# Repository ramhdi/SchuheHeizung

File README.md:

# SchuheHeizung
DIY Thermostat - Applicable for shoe dryer, sous vide cooker, etc

## Arduino codes
- SchuheHeizung v1: first version, heating controlled by user via Blynk app, microcontroller using NodeMCU
- SchuheHeizung v2: offline heating control, uses OLED display and rotary encoder as user interface, microcontroller using Arduino Nano

## PCB files
- SH v1: first version, microcontroller using NodeMCU, controls DC fan and heater
- SH v2: microcontroller using Arduino Nano, controls AC fan and heater
- SH v3: microcontroller using NodeMCU, controls AC fan and heater

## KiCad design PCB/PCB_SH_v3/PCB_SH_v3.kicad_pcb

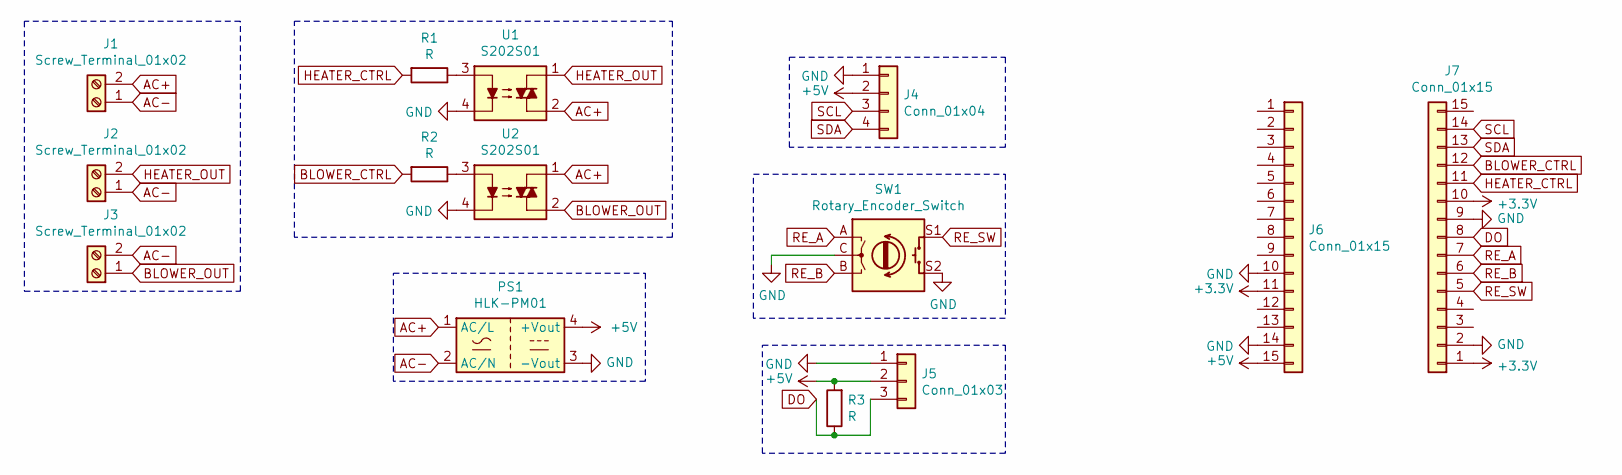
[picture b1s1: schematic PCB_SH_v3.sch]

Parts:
J1, J2, J3: Screw_Terminal_01x02; TerminalBlock_Wuerth_691311400102_P7.62mm
J4: Conn_01x04; PinSocket_1x04_P2.54mm_Vertical
J5: Conn_01x03; PinSocket_1x03_P2.54mm_Vertical
J6, J7: Conn_01x15; PinSocket_1x15_P2.54mm_Vertical
PS1: HLK-PM01; Converter_ACDC_HiLink_HLK-PMxx
R1, R2, R3: R; R_1206_3216Metric_Pad1.42x1.75mm_HandSolder
SW1: Rotary_Encoder_Switch; RotaryEncoder_Alps_EC11E-Switch_Vertical_H20mm
U1, U2: S202S01; SIP4_Sharp-SSR_P7.62mm_Straight

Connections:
+3V3: J6.11, J7.1, J7.10
+5V: J4.2, J5.2, J6.15, PS1.4 (+Vout), R3.2
AC+: J1.2, PS1.1 (AC/L), U1.2, U2.1
AC-: J1.1, J2.1, J3.2, PS1.2 (AC/N)
BLOWER_CTRL: J7.12, R2.2
BLOWER_OUT: J3.1, U2.2
DO: J5.3, J7.8, R3.1
GND: J4.1, J5.1, J6.10, J6.14, J7.2, J7.9, PS1.3 (-Vout), SW1.C, SW1.S2, U1.4, U2.4
HEATER_CTRL: J7.11, R1.2
HEATER_OUT: J2.2, U1.1
unnamed: R1.1, U1.3
unnamed: R2.1, U2.3
RE_A: J7.7, SW1.A
RE_B: J7.6, SW1.B
RE_SW: J7.5, SW1.S1
SCL: J4.3, J7.14
SDA: J4.4, J7.13

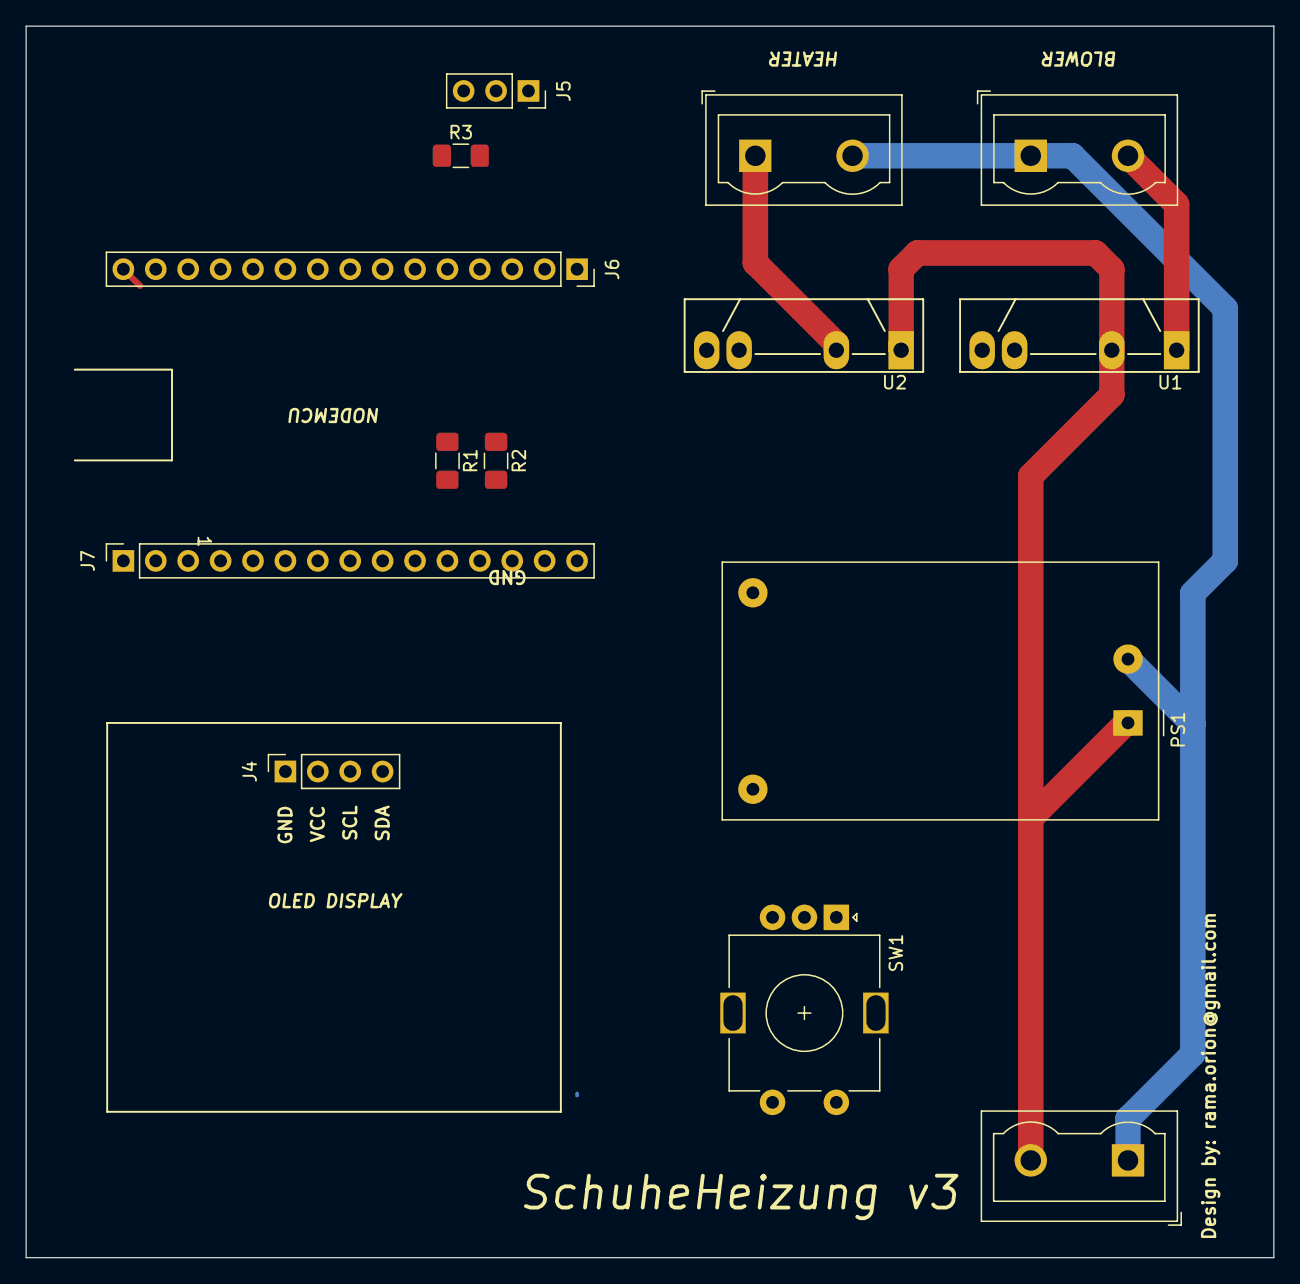
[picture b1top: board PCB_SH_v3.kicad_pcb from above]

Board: 2 copper layers, 97.8 x 96.5 mm, 14 parts (0 on the bottom side), 17 nets.

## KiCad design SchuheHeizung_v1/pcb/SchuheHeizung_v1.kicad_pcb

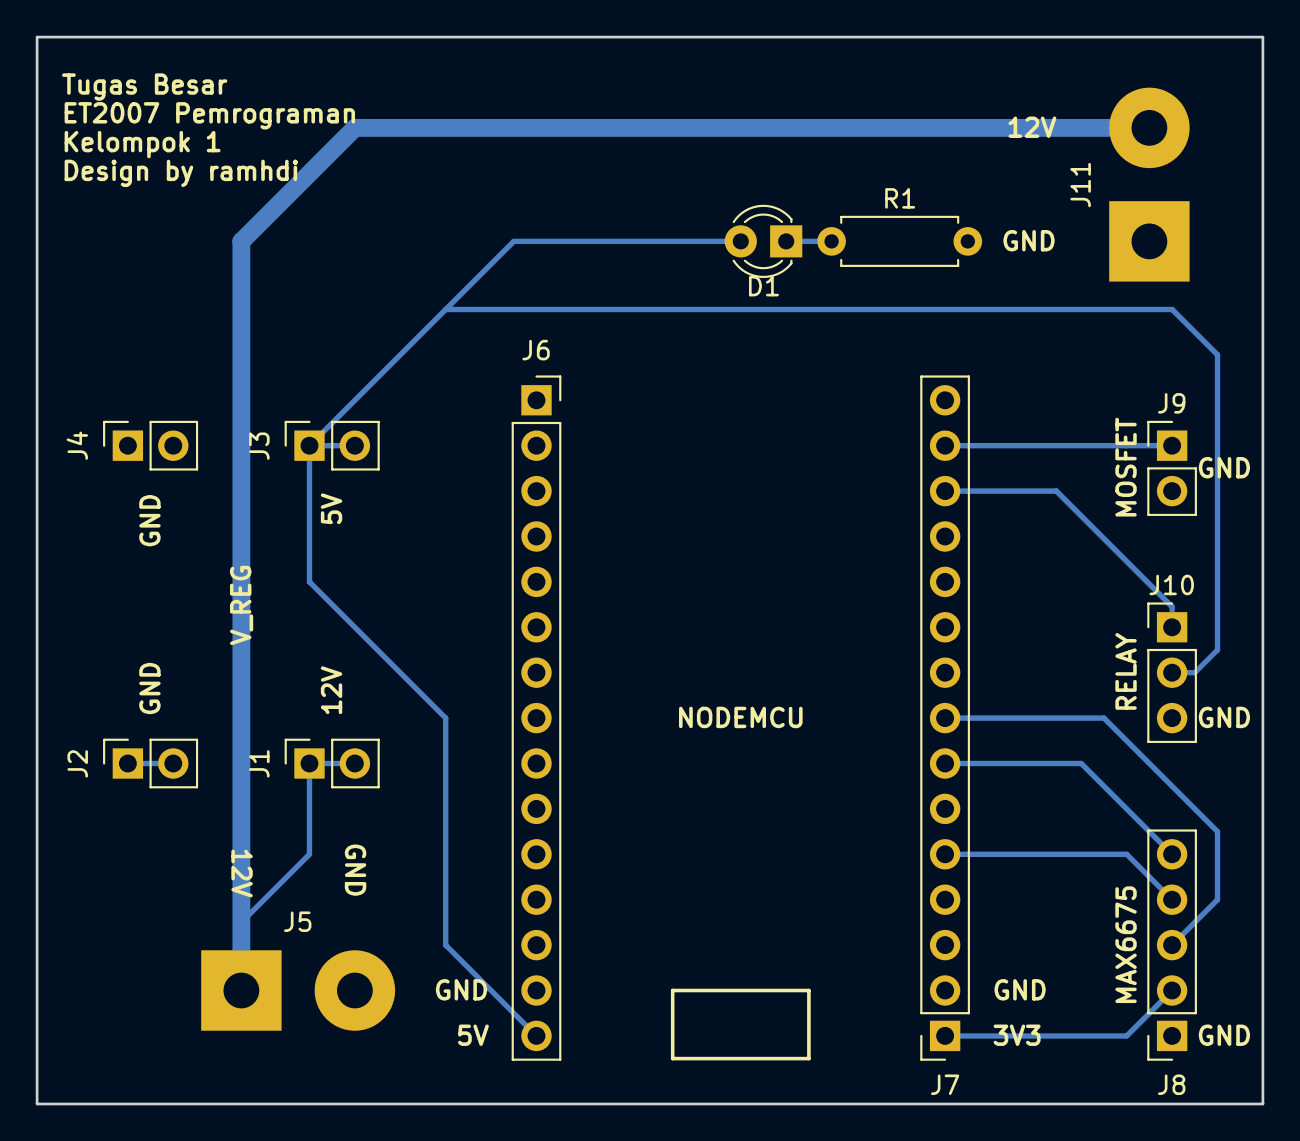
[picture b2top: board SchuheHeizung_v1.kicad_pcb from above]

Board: 2 copper layers, 68.6 x 59.7 mm, 13 parts (0 on the bottom side), 10 nets.

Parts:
D1: LED; LED_D3.0mm
J1, J2, J3, J4: Conn_01x02_Female; PinSocket_1x02_P2.54mm_Vertical
J5, J11: Screw_Terminal_01x02; SolderWirePad_1x02_P7.62mm_Drill2mm
J6, J7: Conn_01x15_Female; PinSocket_1x15_P2.54mm_Vertical
J8: Conn_01x05_Female; PinSocket_1x05_P2.54mm_Vertical
J9: Conn_01x02_Male; PinHeader_1x02_P2.54mm_Vertical
J10: Conn_01x03_Male; PinHeader_1x03_P2.54mm_Vertical
R1: 220; R_Axial_DIN0207_L6.3mm_D2.5mm_P7.62mm_Horizontal

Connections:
+3V3: J6.11, J7.1, J7.10, J8.2
+5V: D1.2, J3.1, J3.2, J6.15, J10.2
+12V: J1.1, J1.2, J5.1, J11.2
CS: J7.5, J8.4
GND: J2.1, J2.2, J4.1, J4.2, J5.2, J6.10, J6.14, J7.2, J7.9, J8.1, J9.2, J10.3, J11.1, R1.2
MOSFET: J7.14, J9.1
unnamed: D1.1, R1.1
RELAY: J7.13, J10.1
SCK: J7.8, J8.3
SO: J7.7, J8.5

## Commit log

2018-12-06 Rename SchuheHeizung_v1.ino to SchuheHeizung_v1/SchuheHeizung_v1.ino
2018-12-07 Added future version
2019-06-13 Reorganized repo
2019-06-13 New PCB v3 files
2019-10-25 Added preheating feature
